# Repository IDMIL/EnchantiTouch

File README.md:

# EnchantiTouch
This repository contains hardware files and firmware for the EnchantiTouch board. EnchantiTouch is a touch sensing board using Cypress' 4100S Max SoC. It supports up to 60 touch sensors through two 32 pin FFC connectors and multichannel scanning.

Branch archive-v0 features firmware for the first iteration of this board which did not have an SPI interface for communicating with a host MCU.

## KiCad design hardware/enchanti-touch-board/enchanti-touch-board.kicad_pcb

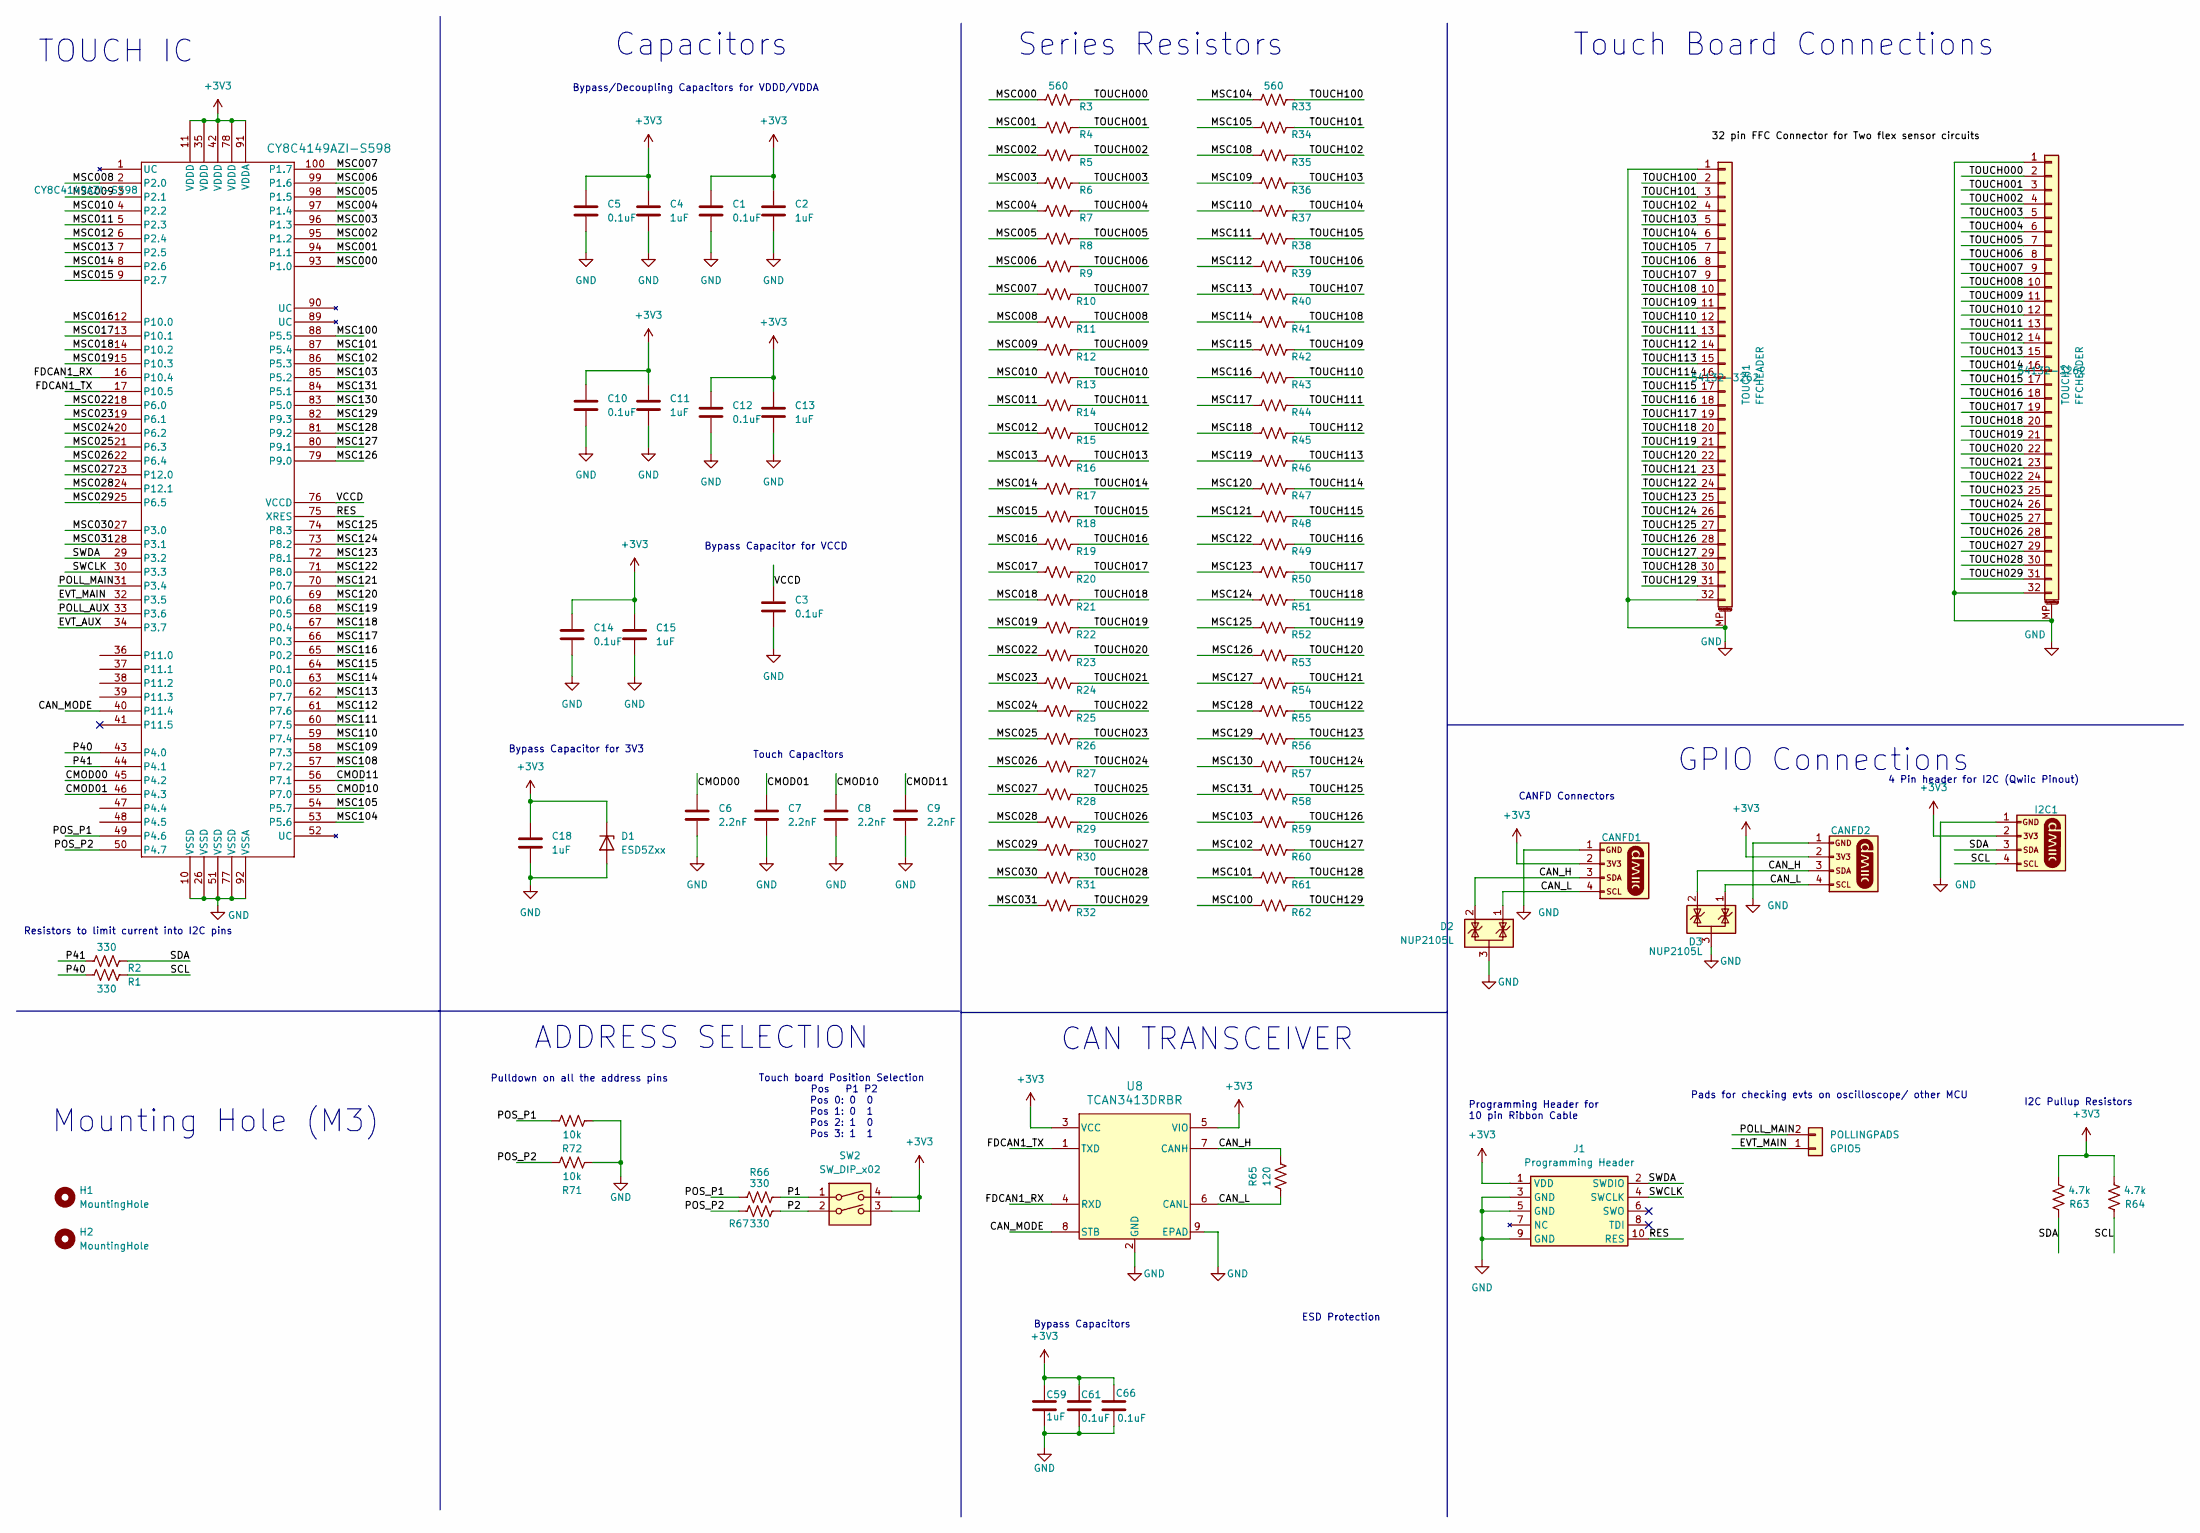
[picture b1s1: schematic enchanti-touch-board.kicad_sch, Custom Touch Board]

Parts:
C1, C3, C5, C10, C12, C14: 0.1uF; C_0402_1005Metric; MPN GCM155R71C104KA55J
C2, C4, C11, C13, C15, C18: 1uF; C_0402_1005Metric; MPN GRM155R61C105KA12D
C6, C7, C8, C9: 2.2nF; C_0402_1005Metric; MPN GRM155R71H222JA01J
C59: 1uF; C_0402_1005Metric; Mfg Part # GRM155R61C105KA12D
C61, C66: 0.1uF; C_0402_1005Metric; Mfg Part # GCM155R71C104KA55J
CANFD1, CANFD2: JST-SH-1x04 1.0mm; JST_SMD_1.0mm-4_Vertical; Mfg Part # BM04B-SRSS-TB
D1: ESD5Zxx; D_SOD-523; MPN ESD5V0D5-TP
D2, D3: NUP2105L; SOT-23; Mfg Part # NUP2105L
GPIO5: POLLINGPADS; solderpads
H1, H2: MountingHole; MountingHole_3.2mm_M3
I2C1: JST-SH-1x04 1.0mm; JST_SMD_1.0mm-4_Vertical; Mfg Part # BM04B-SRSS-TB
J1: Programming Header; SAMTEC_FTSH-105-01-F-DV-P-TR; Mfg Part # FTSH-105-01-F-DV-K-TR
R1, R2, R66, R67: 330; R_0201_0603Metric; MPN ERJ-1GNF3300C
R3, R4, R5, R6, R7, R8, R9, R10, R11, R12, R13, R14, R15, R16, R17, R18, R19, R20, R21, R22, R23, R24, R25, R26, R27, R28, R29, R30, R31, R32, R33, R34, R35, R36, R37, R38, R39, R40, R41, R42, R43, R44, R45, R46, R47, R48, R49, R50, R51, R52, R53, R54, R55, R56, R57, R58, R59, R60, R61, R62: 560; R_0201_0603Metric; MPN ERJ-1GNF5600C
R63, R64: 4.7k; R_0201_0603Metric; MPN ERJ-1GNF4701C
R65: 120; R_0805_2012Metric_Pad1.20x1.40mm_HandSolder; Mfg Part # ERA-6AEB121V
R71, R72: 10k; R_0402_1005Metric; Mfg Part # ERJ-2RKF1002X
SW2: SW_DIP_x02; TDA02H0SB1R_CNK; Mfg Part # TDA02H0SB1R
TOUCH1, TOUCH2: FFCHEADER; CON_541323262_MOL; MPN 54132-3262
U1: CY8C4149AZI-S598; QFP-100; MPN CY8C4149AZI-S598
U8: TCAN3413DRBR; VSON8-DRB_TEX; Mfg Part # TCAN3413DRBR

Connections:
+3V3: C1.2, C2.2, C4.2, C5.2, C10.2, C11.2, C12.2, C13.2, C14.2, C15.2, C18.2, C59.1, C61.1, C66.1, CANFD1.2 (3v3), CANFD2.2 (3v3), D1.1 (K), I2C1.2 (3v3), J1.1 (VDD), R63.2, R64.2, SW2.3, SW2.4, U1.11 (VDDD), U1.35 (VDDD), U1.42 (VDDD), U1.78 (VDDD), U1.91 (VDDA), U8.3 (VCC), U8.5 (VIO)
/CAN_H: CANFD1.3 (SDA), CANFD2.3 (SDA), D2.2 (K), D3.2 (K), R65.2, U8.7 (CANH)
/CAN_L: CANFD1.4 (SCL), CANFD2.4 (SCL), D2.1 (K), D3.1 (K), R65.1, U8.6 (CANL)
/CAN_MODE: U1.40 (P11.4), U8.8 (STB)
/CMOD00: C6.2, U1.45 (P4.2)
/CMOD01: C7.2, U1.46 (P4.3)
/CMOD10: C8.2, U1.55 (P7.0)
/CMOD11: C9.2, U1.56 (P7.1)
/EVT_AUX: U1.34 (P3.7)
/EVT_MAIN: GPIO5.1, U1.32 (P3.5)
/FDCAN1_RX: U1.16 (P10.4), U8.4 (RXD)
/FDCAN1_TX: U1.17 (P10.5), U8.1 (TXD)
/MSC000: R3.1, U1.93 (P1.0)
/MSC001: R4.1, U1.94 (P1.1)
/MSC002: R5.1, U1.95 (P1.2)
/MSC003: R6.1, U1.96 (P1.3)
/MSC004: R7.1, U1.97 (P1.4)
/MSC005: R8.1, U1.98 (P1.5)
/MSC006: R9.1, U1.99 (P1.6)
/MSC007: R10.1, U1.100 (P1.7)
/MSC008: R11.1, U1.2 (P2.0)
/MSC009: R12.1, U1.3 (P2.1)
/MSC010: R13.1, U1.4 (P2.2)
/MSC011: R14.1, U1.5 (P2.3)
/MSC012: R15.1, U1.6 (P2.4)
/MSC013: R16.1, U1.7 (P2.5)
/MSC014: R17.1, U1.8 (P2.6)
/MSC015: R18.1, U1.9 (P2.7)
/MSC016: R19.1, U1.12 (P10.0)
/MSC017: R20.1, U1.13 (P10.1)
/MSC018: R21.1, U1.14 (P10.2)
/MSC019: R22.1, U1.15 (P10.3)
/MSC022: R23.1, U1.18 (P6.0)
/MSC023: R24.1, U1.19 (P6.1)
/MSC024: R25.1, U1.20 (P6.2)
/MSC025: R26.1, U1.21 (P6.3)
/MSC026: R27.1, U1.22 (P6.4)
/MSC027: R28.1, U1.23 (P12.0)
/MSC028: R29.1, U1.24 (P12.1)
/MSC029: R30.1, U1.25 (P6.5)
/MSC030: R31.1, U1.27 (P3.0)
/MSC031: R32.1, U1.28 (P3.1)
/MSC100: R62.1, U1.88 (P5.5)
/MSC101: R61.1, U1.87 (P5.4)
/MSC102: R60.1, U1.86 (P5.3)
/MSC103: R59.1, U1.85 (P5.2)
/MSC104: R33.1, U1.53 (P5.6)
/MSC105: R34.1, U1.54 (P5.7)
/MSC108: R35.1, U1.57 (P7.2)
/MSC109: R36.1, U1.58 (P7.3)
/MSC110: R37.1, U1.59 (P7.4)
/MSC111: R38.1, U1.60 (P7.5)
/MSC112: R39.1, U1.61 (P7.6)
/MSC113: R40.1, U1.62 (P7.7)
/MSC114: R41.1, U1.63 (P0.0)
/MSC115: R42.1, U1.64 (P0.1)
/MSC116: R43.1, U1.65 (P0.2)
/MSC117: R44.1, U1.66 (P0.3)
/MSC118: R45.1, U1.67 (P0.4)
/MSC119: R46.1, U1.68 (P0.5)
/MSC120: R47.1, U1.69 (P0.6)
/MSC121: R48.1, U1.70 (P0.7)
/MSC122: R49.1, U1.71 (P8.0)
/MSC123: R50.1, U1.72 (P8.1)
/MSC124: R51.1, U1.73 (P8.2)
/MSC125: R52.1, U1.74 (P8.3)
/MSC126: R53.1, U1.79 (P9.0)
/MSC127: R54.1, U1.80 (P9.1)
/MSC128: R55.1, U1.81 (P9.2)
/MSC129: R56.1, U1.82 (P9.3)
/MSC130: R57.1, U1.83 (P5.0)
/MSC131: R58.1, U1.84 (P5.1)
/P1: R66.2, SW2.1
/P2: R67.2, SW2.2
/P40: R1.1, U1.43 (P4.0)
/P41: R2.1, U1.44 (P4.1)
/POLL_AUX: U1.33 (P3.6)
/POLL_MAIN: GPIO5.2, U1.31 (P3.4)
/POS_P1: R66.1, R72.2, U1.49 (P4.6)
/POS_P2: R67.1, R71.2, U1.50 (P4.7)
/RES: J1.10 (RES), U1.75 (XRES)
/SCL: I2C1.4 (SCL), R1.2, R64.1
/SDA: I2C1.3 (SDA), R2.2, R63.1
/SWCLK: J1.4 (SWCLK), U1.30 (P3.3)
/SWDA: J1.2 (SWDIO), U1.29 (P3.2)
/TOUCH000: R3.2, TOUCH2.2
/TOUCH001: R4.2, TOUCH2.3
/TOUCH002: R5.2, TOUCH2.4
/TOUCH003: R6.2, TOUCH2.5
/TOUCH004: R7.2, TOUCH2.6
/TOUCH005: R8.2, TOUCH2.7
/TOUCH006: R9.2, TOUCH2.8
/TOUCH007: R10.2, TOUCH2.9
/TOUCH008: R11.2, TOUCH2.10
/TOUCH009: R12.2, TOUCH2.11
/TOUCH010: R13.2, TOUCH2.12
/TOUCH011: R14.2, TOUCH2.13
/TOUCH012: R15.2, TOUCH2.14
/TOUCH013: R16.2, TOUCH2.15
/TOUCH014: R17.2, TOUCH2.16
/TOUCH015: R18.2, TOUCH2.17
/TOUCH016: R19.2, TOUCH2.18
/TOUCH017: R20.2, TOUCH2.19
/TOUCH018: R21.2, TOUCH2.20
/TOUCH019: R22.2, TOUCH2.21
/TOUCH020: R23.2, TOUCH2.22
/TOUCH021: R24.2, TOUCH2.23
/TOUCH022: R25.2, TOUCH2.24
/TOUCH023: R26.2, TOUCH2.25
/TOUCH024: R27.2, TOUCH2.26
/TOUCH025: R28.2, TOUCH2.27
/TOUCH026: R29.2, TOUCH2.28
/TOUCH027: R30.2, TOUCH2.29
/TOUCH028: R31.2, TOUCH2.30
/TOUCH029: R32.2, TOUCH2.31
/TOUCH100: R33.2, TOUCH1.2
/TOUCH101: R34.2, TOUCH1.3
/TOUCH102: R35.2, TOUCH1.4
/TOUCH103: R36.2, TOUCH1.5
/TOUCH104: R37.2, TOUCH1.6
/TOUCH105: R38.2, TOUCH1.7
/TOUCH106: R39.2, TOUCH1.8
/TOUCH107: R40.2, TOUCH1.9
/TOUCH108: R41.2, TOUCH1.10
/TOUCH109: R42.2, TOUCH1.11
/TOUCH110: R43.2, TOUCH1.12
/TOUCH111: R44.2, TOUCH1.13
/TOUCH112: R45.2, TOUCH1.14
/TOUCH113: R46.2, TOUCH1.15
/TOUCH114: R47.2, TOUCH1.16
/TOUCH115: R48.2, TOUCH1.17
/TOUCH116: R49.2, TOUCH1.18
/TOUCH117: R50.2, TOUCH1.19
/TOUCH118: R51.2, TOUCH1.20
/TOUCH119: R52.2, TOUCH1.21
/TOUCH120: R53.2, TOUCH1.22
/TOUCH121: R54.2, TOUCH1.23
/TOUCH122: R55.2, TOUCH1.24
/TOUCH123: R56.2, TOUCH1.25
/TOUCH124: R57.2, TOUCH1.26
/TOUCH125: R58.2, TOUCH1.27
/TOUCH126: R59.2, TOUCH1.28
/TOUCH127: R60.2, TOUCH1.29
/TOUCH128: R61.2, TOUCH1.30
/TOUCH129: R62.2, TOUCH1.31
/VCCD: C3.2, U1.76 (VCCD)
GND: C1.1, C2.1, C3.1, C4.1, C5.1, C6.1, C7.1, C8.1, C9.1, C10.1, C11.1, C12.1, C13.1, C14.1, C15.1, C18.1, C59.2, C61.2, C66.2, CANFD1.1 (GND), CANFD2.1 (GND), D1.2 (A), D2.3 (A), D3.3 (A), I2C1.1 (GND), J1.3 (GND), J1.5 (GND), J1.9 (GND), R71.1, R72.1, TOUCH1.1, TOUCH1.32, TOUCH1.MP (MountPin), TOUCH2.1, TOUCH2.32, TOUCH2.MP (MountPin), U1.10 (VSSD), U1.26 (VSSD), U1.51 (VSSD), U1.77 (VSSD), U1.92 (VSSA), U8.2 (GND), U8.9 (EPAD)

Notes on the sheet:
Bypass Capacitor for VCCD
Touch Board Connections
ADDRESS SELECTION
Capacitors
Bypass Capacitors
Bypass/Decoupling Capacitors for VDDD/VDDA
Pads for checking evts on oscilloscope/ other MCU
GPIO Connections
CAN TRANSCEIVER
ESD Protection
Bypass Capacitor for 3V3
Mounting Hole (M3)
Touch Capacitors
Resistors to limit current into I2C pins
CANFD Connectors
Pulldown on all the address pins
Series Resistors
I2C Pullup Resistors
4 Pin header for I2C (Qwiic Pinout)
TOUCH IC
Programming Header for 10 pin Ribbon Cable
Touch board Position Selection Pos P1 P2 Pos 0: 0 0 Pos 1: 0 1 Pos 2: 1 0 Pos 3: 1 1

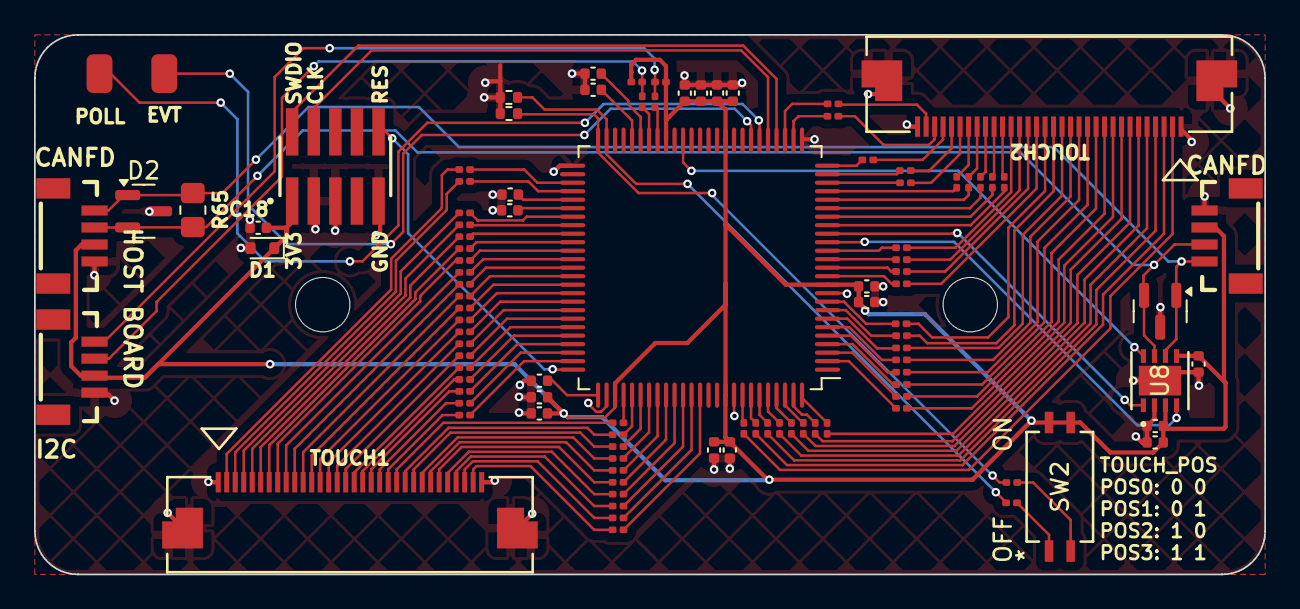
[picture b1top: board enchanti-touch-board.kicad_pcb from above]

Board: 2 copper layers, 72.4 x 31.8 mm, 103 parts (0 on the bottom side), 145 nets.

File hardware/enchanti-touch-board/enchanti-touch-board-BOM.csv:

"Reference","Value","Qty","Manufacturer","Mfg Part #","Description"
"C1,C3,C5,C10,C12,C14,C61,C66","0.1uF","8","Murata Electronics","GCM155R71C104KA55J","0.1 µF ±10% 16V Ceramic Capacitor X7R 0402 (1005 Metric)"
"C2,C4,C11,C13,C15,C18,C59","1uF","7","Murata Electronics","GRM155R61C105KA12D","1 µF ±10% 16V Ceramic Capacitor X5R 0402 (1005 Metric)"
"C6,C7,C8,C9","2.2nF","4","Murata Electronics","GRM155R71H222JA01J","2200 pF ±5% 50V Ceramic Capacitor X7R 0402 (1005 Metric)"
"CANFD1,CANFD2,I2C1","JST-SH-1x04 1.0mm","3","JST Sales America Inc.","BM04B-SRSS-TB","Connector Header Surface Mount 4 position 0.039"" (1.00mm)"
"D1","ESD5Zxx","1","Micro Commercial Co","ESD5V0D5-TP","18.6V Clamp 11.6A (8/20µs) Ipp Tvs Diode Surface Mount SOD-523"
"D2,D3","NUP2105L","2","Diotec Semiconductor","NUP2105L","44V Clamp 8A (8/20µs) Ipp Tvs Diode Surface Mount SOT-23-3 (TO-236)"
"J1","Programming Header","1","Samtec Inc.","FTSH-105-01-F-DV-K-TR","Connector Header Surface Mount 10 position 0.050"" (1.27mm)"
"R1,R2,R66,R67","330","4","Panasonic Electronic Components","ERJ-1GNF3300C","330 Ohms ±1% 0.05W, 1/20W Chip Resistor 0201 (0603 Metric) Thick Film"
"R3,R4,R5,R6,R7,R8,R9,R10,R11,R12,R13,R14,R15,R16,R17,R18,R19,R20,R21,R22,R23,R24,R25,R26,R27,R28,R29,R30,R31,R32,R33,R34,R35,R36,R37,R38,R39,R40,R41,R42,R43,R44,R45,R46,R47,R48,R49,R50,R51,R52,R53,R54,R55,R56,R57,R58,R59,R60,R61,R62","560","60","Panasonic Electronic Components","ERJ-1GNF5600C","560 Ohms ±1% 0.05W, 1/20W Chip Resistor 0201 (0603 Metric) Thick Film"
"R63,R64","4.7k","2","Panasonic Electronic Components","ERJ-1GNF4701C","4.7 kOhms ±1% 0.05W, 1/20W Chip Resistor 0201 (0603 Metric) Thick Film"
"R65","120","1","Panasonic Electronic Components","ERA-6AEB121V","120 Ohms ±0.1% 0.125W, 1/8W Chip Resistor 0805 (2012 Metric) Automotive AEC-Q200 Thin Film"
"R71,R72","10k","2","Panasonic Electronic Components","ERJ-2RKF1002X","10 kOhms ±1% 0.1W, 1/10W Chip Resistor 0402 (1005 Metric) Automotive AEC-Q200 Thick Film"
"SW2","SW_DIP_x02","1","C&K","TDA02H0SB1R","2x DIP Switch, Single Pole Single Throw (SPST) switch, small symbol"
"TOUCH1,TOUCH2","FFCHEADER","2","Molex","54132-3262","32 Position FFC, FPC Connector Contacts, Bottom 0.020"" (0.50mm) Surface Mount, Right Angle"
"U1","CY8C4149AZI-S598","1","Infineon Technologies","CY8C4149AZI-S598","ARM® Cortex®-M0+ PSOC® 4 CY8C4100S Microcontroller IC 32-Bit 48MHz 384KB (384K x 8) FLASH 100-TQFP (14x14)"
"U8","TCAN3413DRBR","1","Texas Instruments","TCAN3413DRBR","1/1 Transceiver Half CANbus 8-SON (3x3)"

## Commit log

2024-01-11 add old firmware
2024-01-11 moved firmware files to the right folder
2024-01-11 removed mtbquery file, updated board definitions for new board
2024-01-13 updated SPI touch buffers, switch makefile to release
2024-01-14 added code to measure scan time
    scan time between 0.853 to 1.2 ms
2024-02-05 changed SPI code to be non blocking
2024-03-30 Update LICENSE
2025-03-20 Updated manufacturing files for board-rev3, added CANFD connector from board, removed redundant I2C connector
2026-03-09 Updated code for revision 0.3 of the boards, canfd bus doesn't seem to be working
2026-03-09 Ignore all the dependency folders
2026-03-10 Initial code with working canfd bus, values at edges not being read, remove logfile and add it to gitignore
2026-03-10 remove mtbquery file and add to gitignore
2026-03-10 Added board config structure to send board config in 4 bytes as the first element of the data buffer
2026-03-10 Remove unneeded newData = 0
2026-03-10 Increased CANFD bitrate to 4Mbps
2026-03-10 Added scantime to i2c registers
2026-03-11 Changed the CPU state to always be in active state
2026-03-11 Added comments to schematics for improvements in Rev 0.4
